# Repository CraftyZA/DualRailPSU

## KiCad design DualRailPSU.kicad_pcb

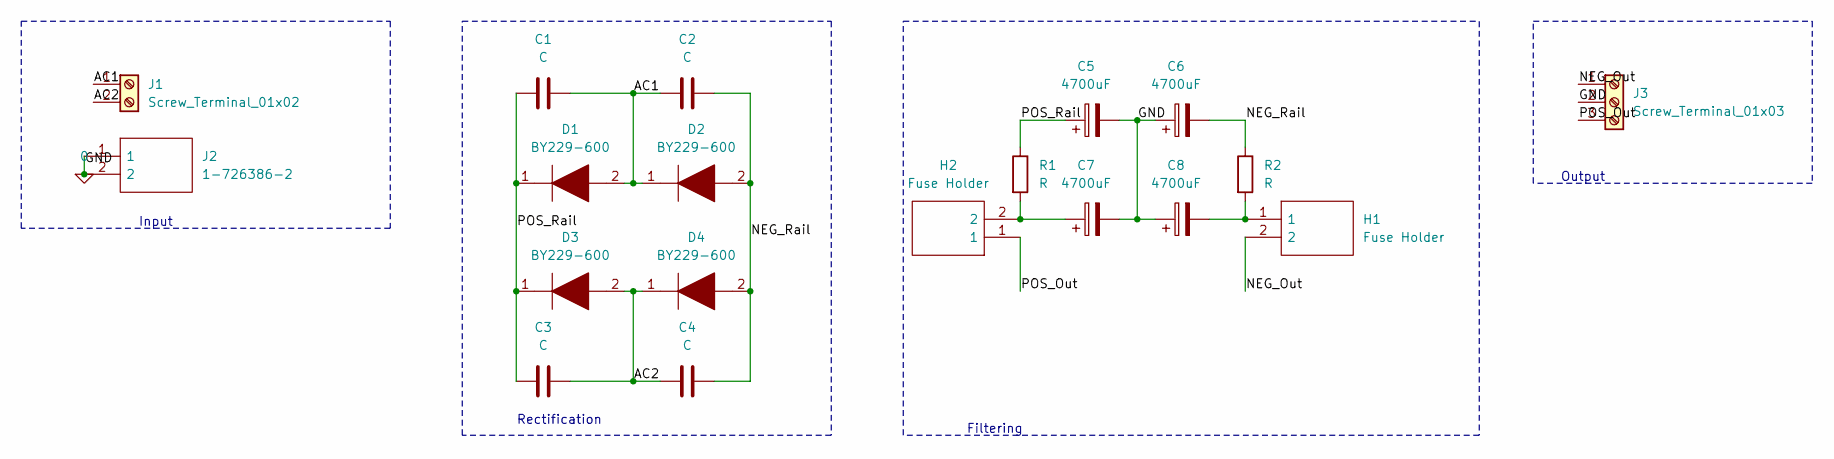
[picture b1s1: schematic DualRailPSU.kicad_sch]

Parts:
C1, C2, C3, C4: C; C_Disc_D4.3mm_W1.9mm_P5.00mm
C5, C6, C7, C8: 4700uF; CP_Radial_D26.0mm_P10.00mm_SnapIn
D1, D2, D3, D4: BY229-600; TO-220-2_Vertical; Manufacturer_Part_Number BY229-600; Mouser Part Number 771-BY229-600
H1, H2: Fuse Holder; 65600001009; Manufacturer_Part_Number 65600001009; Mouser Part Number 576-65600001009
J1: Screw_Terminal_01x02; TerminalBlock_Phoenix_PT-1,5-2-5.0-H_1x02_P5.00mm_Horizontal
J2: 1-726386-2; 17263862; Manufacturer_Part_Number 1-726386-2; Mouser Part Number 571-1-726386-2
J3: Screw_Terminal_01x03; TerminalBlock_Phoenix_MKDS-1,5-3-5.08_1x03_P5.08mm_Horizont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
R1, R2: R; R_Axial_DIN0414_L11.9mm_D4.5mm_P20.32mm_Horizontal

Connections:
0: C5.2, C6.1, C7.2, C8.1, J2.1, J2.2, J3.2
/AC1: C1.2, C2.1, D1.2, D2.1, J1.1
/AC2: C3.2, C4.1, D3.2, D4.1, J1.2
/NEG_Out: H1.2, J3.1
/NEG_Rail: C2.2, C4.2, C6.2, D2.2, D4.2, R2.1
/POS_Out: H2.1, J3.3
/POS_Rail: C1.1, C3.1, C5.1, D1.1, D3.1, R1.1
unnamed: C7.1, H2.2, R1.2
unnamed: C8.2, H1.1, R2.2

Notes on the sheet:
Filtering
Input
Rectification
Output

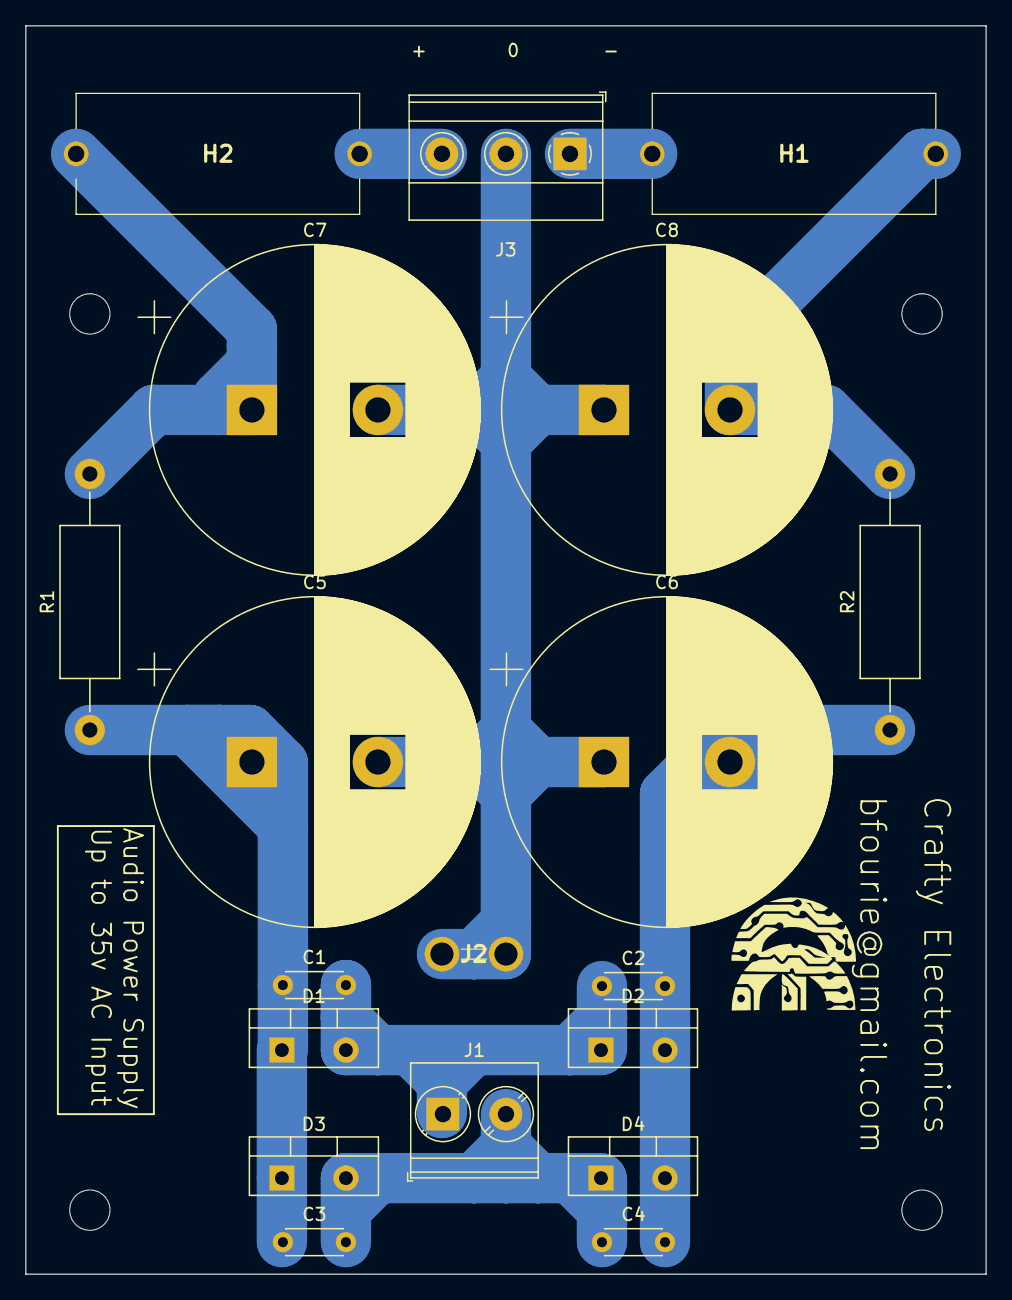
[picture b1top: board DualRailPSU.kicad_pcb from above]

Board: 2 copper layers, 76.2 x 99.1 mm, 19 parts (0 on the bottom side), 9 nets.

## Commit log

2024-07-27 added screenshot
2024-07-30 Fixed output terminal block orientation, and moved text and logo to silscreen front layer
